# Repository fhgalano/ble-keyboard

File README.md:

# Overview 

This is an implementation of a bluetooth keyboard on an ESP32-C3 Devkit

# Code 

This was developed in conjunction with [keyboard](https://github.com/fhgalano/keyboard)

I'm using [esp32-nimble](https://github.com/taks/esp32-nimble) to handle the bluetooth conection. Most of the bluetooth connection code is taken from the examples. 

# Mechanical

I've been having fun with kicad scripting - I like the consistency it creates. It also helps with the tedious parts of routing a bunch of keyboard keys. Feel free to check it out [here](https://github.com/fhgalano/kicad-utilities), but I would describe the code as 'certified jank'

The PCB for the keyboard is reversible and uses cherry mx compatible hotswap sockets. It uses most of the gpio pins available on the devkit, but any remaining pins are made available through jst ph-k through hole connectors. It's also only two layers to make it cheaper to iterate through.

_**as of Feb 2025 I have only just placed the order for the first revision of the pcb, so I have no idea if it works. Use at your own risk. I'll update once I get it.**_

*Update: the board works but also has some large flaws - the biggest of which being that the devkit is positioned such that I need to remove several keys in order to program it. I'm lucky that I made this with hotswaps. I don't plan to update the board for a while, despite the flaws - I'll be implementing some new features (quick switching between bonded devices, power saving, using multiple devices as one wirelessly, layer indication leds, timers instead of blocking delays, and other stuff I notice while using it). Once those are done, then I'll look at redesigning the board*

I plan to make documentation eventually, since it's good practice. However, it isn't a huge priority since I am literally the only person aware that this project exists. Also, anyone looking to make a keyboard should probably be using something more feature rich like QMK, RMK, or Keyberon. Nevertheless, if documentation would help your project/learning then I'd be happy to add it in.

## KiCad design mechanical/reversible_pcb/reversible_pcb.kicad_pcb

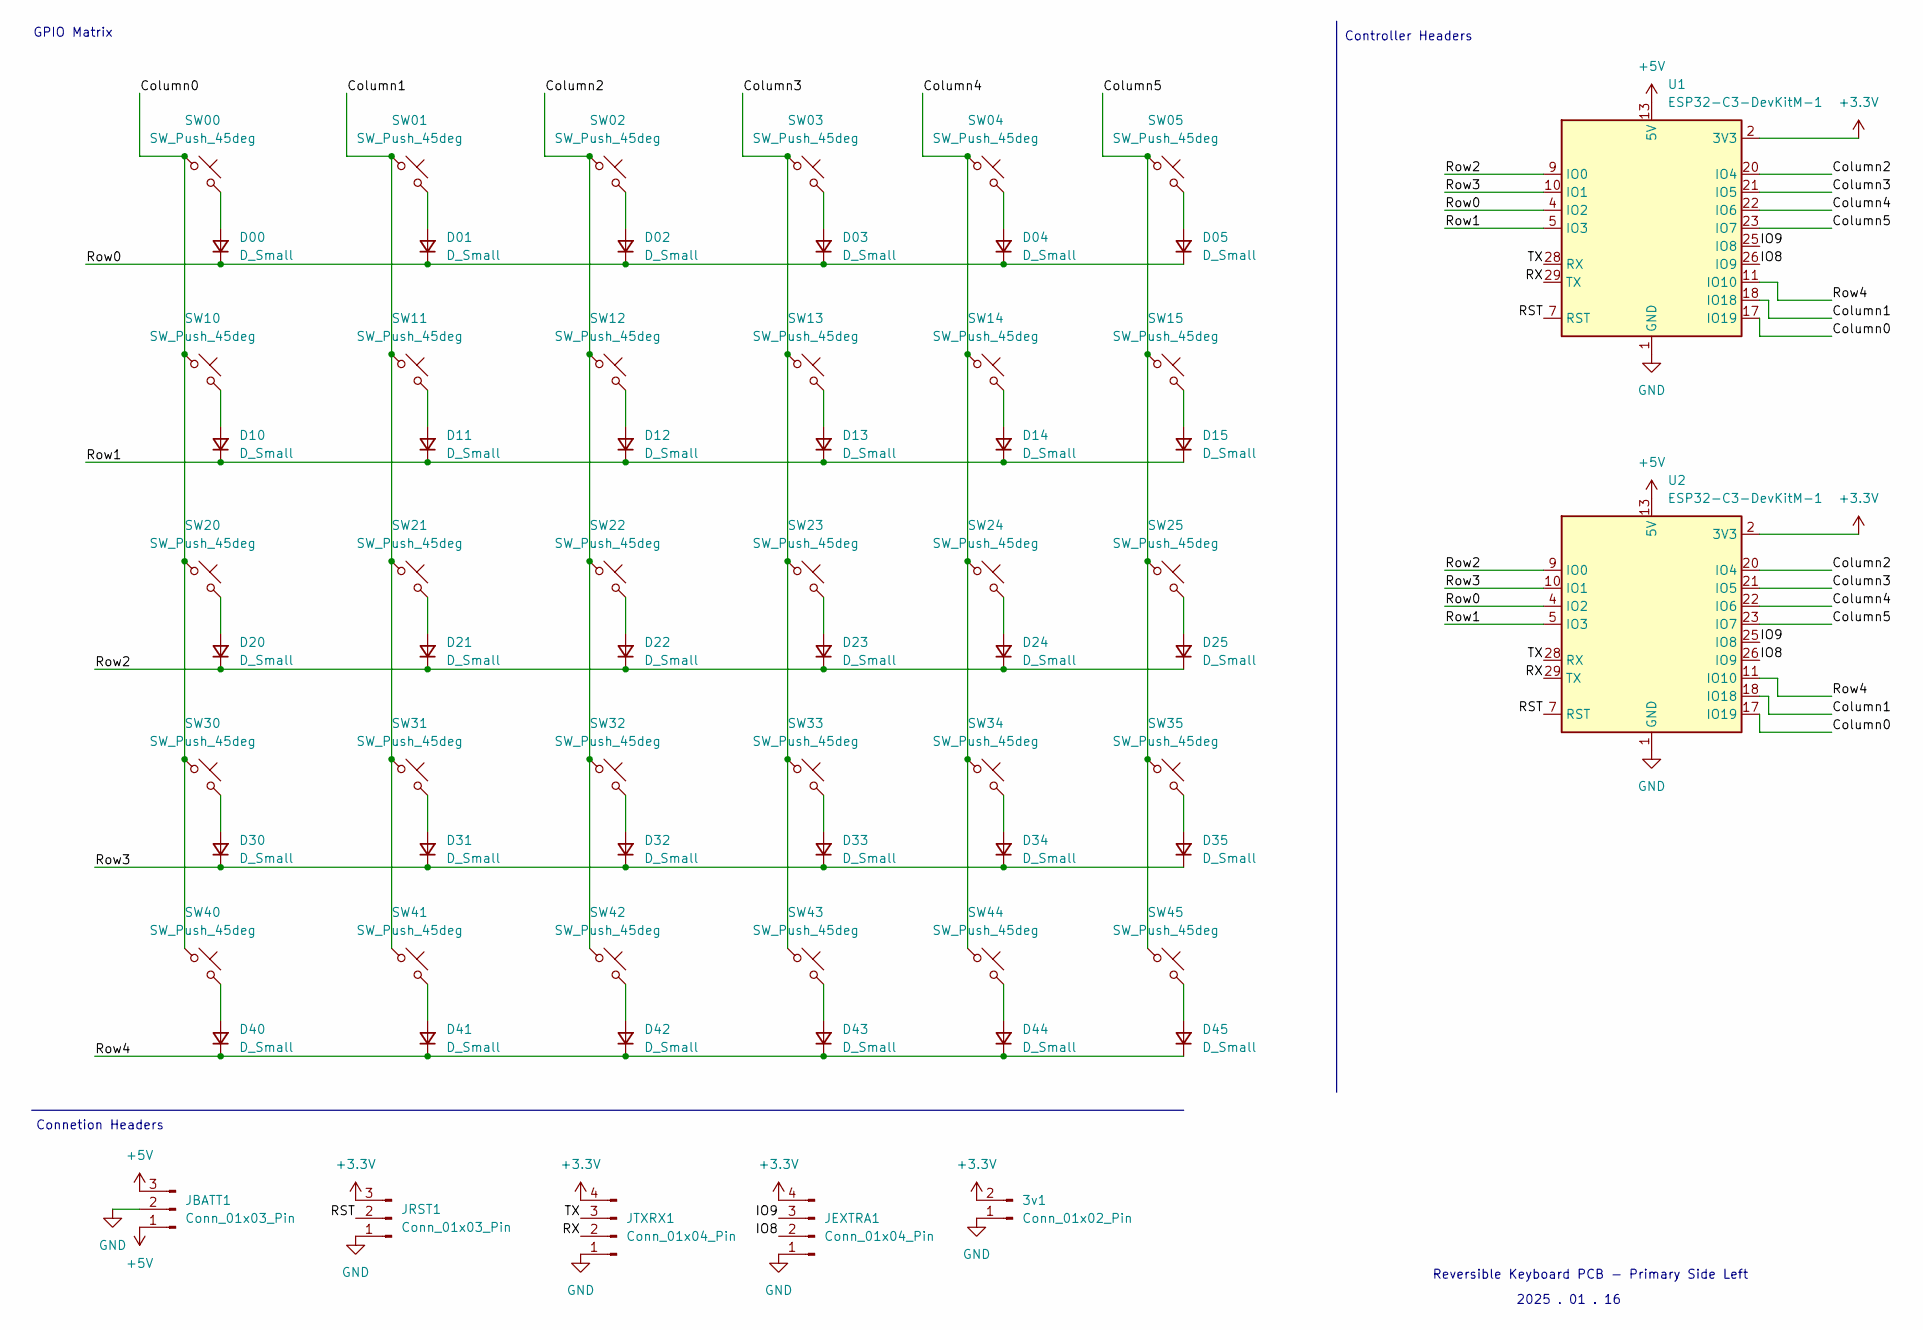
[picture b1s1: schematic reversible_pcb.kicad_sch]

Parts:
3v1: Conn_01x02_Pin; JST_PH_S2B-PH-K_1x02_P2.00mm_Horizontal
D00, D01, D02, D03, D04, D05, D10, D11, D12, D13, D14, D15, D20, D21, D22, D23, D24, D25, D30, D31, D32, D33, D34, D35, D40, D41, D42, D43, D44, D45: D_Small; D_T-1_P5.08mm_Horizontal_Double_Silkscreen
JBATT1: Conn_01x03_Pin; JST_PH_S3B-PH-K_1x03_P2.00mm_Horizontal
JEXTRA1: Conn_01x04_Pin; JST_PH_S4B-PH-K_1x04_P2.00mm_Horizontal
JRST1: Conn_01x03_Pin; JST_PH_S3B-PH-K_1x03_P2.00mm_Horizontal
JTXRX1: Conn_01x04_Pin; JST_PH_S4B-PH-K_1x04_P2.00mm_Horizontal
SW00, SW01, SW02, SW03, SW04, SW10, SW11, SW12, SW13, SW14, SW20, SW21, SW22, SW23, SW24, SW30, SW31, SW32, SW33, SW34, SW40, SW41, SW43, SW44, SW45: SW_Push_45deg; SW_Hotswap_Kailh_MX_reversible_1.00u
SW05, SW15, SW25, SW35: SW_Push_45deg; SW_Hotswap_Kailh_MX_reversible_1.25u
SW42: SW_Push_45deg; SW_Hotswap_Kailh_MX_reversible_1.50u_90deg
U1, U2: ESP32-C3-DevKitM-1

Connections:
+3.3V: 3v1.2, JEXTRA1.4, JRST1.3, JTXRX1.4, U1.2 (3V3), U1.3 (3V3), U2.2 (3V3), U2.3 (3V3)
+5V: JBATT1.1, JBATT1.3, U1.13 (5V), U1.14 (5V), U2.13 (5V), U2.14 (5V)
/Column0: SW00.1, SW10.1, SW20.1, SW30.1, SW40.1, U1.17 (IO19), U2.17 (IO19)
/Column1: SW01.1, SW11.1, SW21.1, SW31.1, SW41.1, U1.18 (IO18), U2.18 (IO18)
/Column2: SW02.1, SW12.1, SW22.1, SW32.1, SW42.1, U1.20 (IO4), U2.20 (IO4)
/Column3: SW03.1, SW13.1, SW23.1, SW33.1, SW43.1, U1.21 (IO5), U2.21 (IO5)
/Column4: SW04.1, SW14.1, SW24.1, SW34.1, SW44.1, U1.22 (IO6), U2.22 (IO6)
/Column5: SW05.1, SW15.1, SW25.1, SW35.1, SW45.1, U1.23 (IO7), U2.23 (IO7)
/IO8: JEXTRA1.2, U1.26 (IO9), U2.26 (IO9)
/IO9: JEXTRA1.3, U1.25 (IO8), U2.25 (IO8)
/RST: JRST1.2, U1.7 (RST), U2.7 (RST)
/RX: JTXRX1.2, U1.29 (TX), U2.29 (TX)
/Row0: D00.1 (K), D01.1 (K), D02.1 (K), D03.1 (K), D04.1 (K), D05.1 (K), U1.4 (IO2), U2.4 (IO2)
/Row1: D10.1 (K), D11.1 (K), D12.1 (K), D13.1 (K), D14.1 (K), D15.1 (K), U1.5 (IO3), U2.5 (IO3)
/Row2: D20.1 (K), D21.1 (K), D22.1 (K), D23.1 (K), D24.1 (K), D25.1 (K), U1.9 (IO0), U2.9 (IO0)
/Row3: D30.1 (K), D31.1 (K), D32.1 (K), D33.1 (K), D34.1 (K), D35.1 (K), U1.10 (IO1), U2.10 (IO1)
/Row4: D40.1 (K), D41.1 (K), D42.1 (K), D43.1 (K), D44.1 (K), D45.1 (K), U1.11 (IO10), U2.11 (IO10)
/TX: JTXRX1.3, U1.28 (RX), U2.28 (RX)
GND: 3v1.1, JBATT1.2, JEXTRA1.1, JRST1.1, JTXRX1.1, U1.1 (GND), U1.6 (GND), U1.8 (GND), U1.12 (GND), U1.15 (GND), U1.16 (GND), U1.19 (GND), U1.24 (GND), U1.27 (GND), U1.30 (GND), U2.1 (GND), U2.6 (GND), U2.8 (GND), U2.12 (GND), U2.15 (GND), U2.16 (GND), U2.19 (GND), U2.24 (GND), U2.27 (GND), U2.30 (GND)
unnamed: D00.2 (A), SW00.2
unnamed: D01.2 (A), SW01.2
unnamed: D02.2 (A), SW02.2
unnamed: D03.2 (A), SW03.2
unnamed: D04.2 (A), SW04.2
unnamed: D05.2 (A), SW05.2
unnamed: D10.2 (A), SW10.2
unnamed: D11.2 (A), SW11.2
unnamed: D12.2 (A), SW12.2
unnamed: D13.2 (A), SW13.2
unnamed: D14.2 (A), SW14.2
unnamed: D15.2 (A), SW15.2
unnamed: D20.2 (A), SW20.2
unnamed: D21.2 (A), SW21.2
unnamed: D22.2 (A), SW22.2
unnamed: D23.2 (A), SW23.2
unnamed: D24.2 (A), SW24.2
unnamed: D25.2 (A), SW25.2
unnamed: D30.2 (A), SW30.2
unnamed: D31.2 (A), SW31.2
unnamed: D32.2 (A), SW32.2
unnamed: D33.2 (A), SW33.2
unnamed: D34.2 (A), SW34.2
unnamed: D35.2 (A), SW35.2
unnamed: D40.2 (A), SW40.2
unnamed: D41.2 (A), SW41.2
unnamed: D42.2 (A), SW42.2
unnamed: D43.2 (A), SW43.2
unnamed: D44.2 (A), SW44.2
unnamed: D45.2 (A), SW45.2

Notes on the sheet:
Reversible Keyboard PCB - Primary Side Left
2025 . 01 . 16
Connetion Headers
Controller Headers
GPIO Matrix

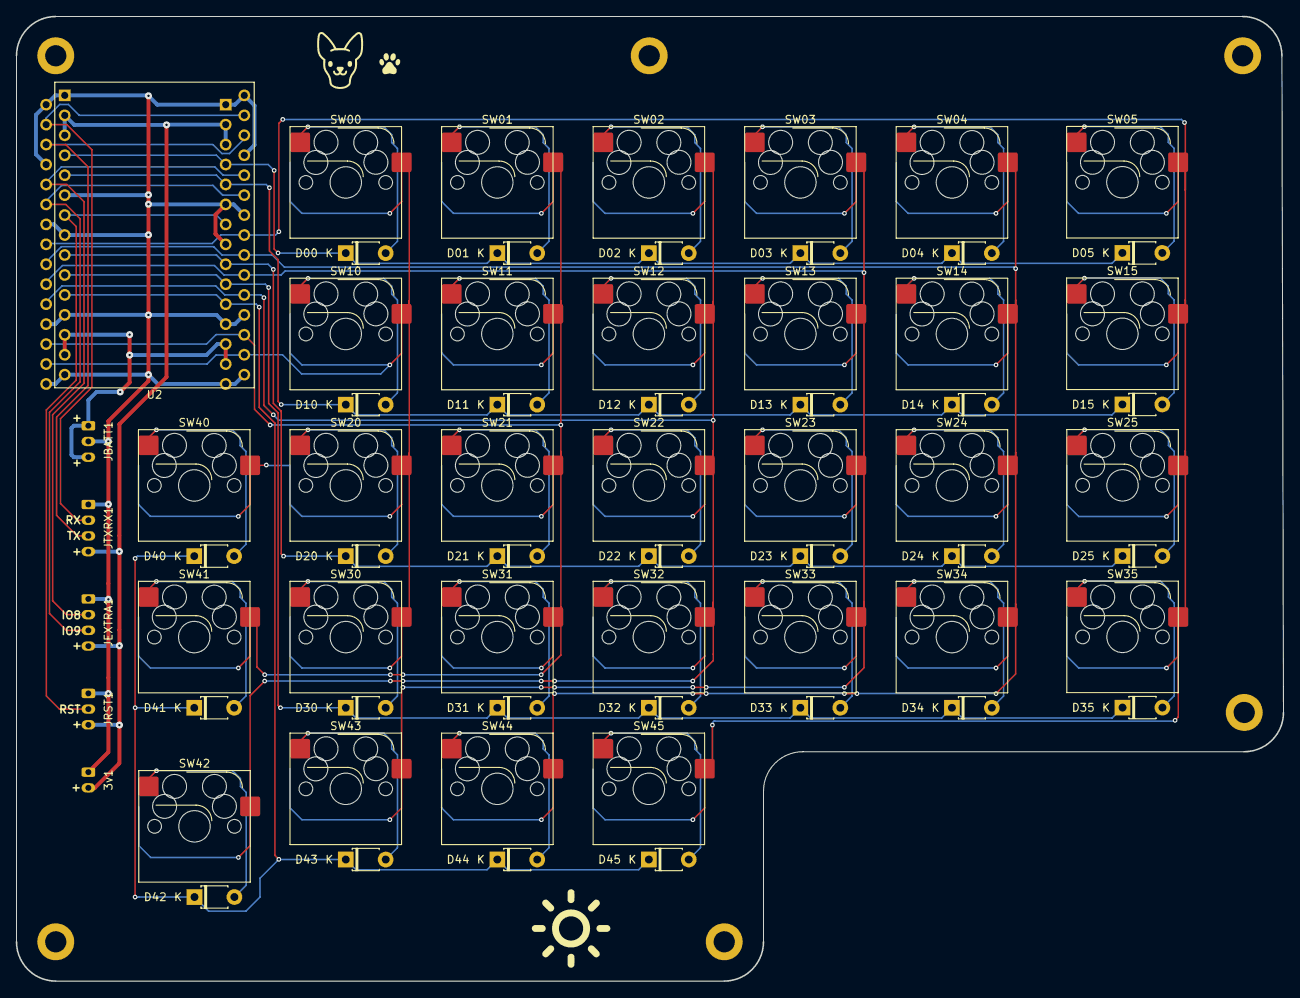
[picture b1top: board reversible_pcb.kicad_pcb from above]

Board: 2 copper layers, 161.3 x 122.8 mm, 67 parts (1 on the bottom side), 49 nets.

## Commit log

2025-01-12 initial commit; keyboard messages send correctly, but is not able to use gpio as input
2025-02-03 fixed polling logic issues
2025-02-03 added kicad files for main board
2025-02-03 fixes for ble connection issues
2025-02-03 added README
2025-02-14 removed backups covered by keyboard lib
2025-03-08 fixed issue related to esp dependencies
2025-03-08 added ios persistence so I could test on my phone
2025-03-08 updated to use correct gpio pins from the pcb, also using new lib features to create layers
2025-03-26 working (ugly) mvp for two keyboard halves acting as one device
2025-03-26 Authors
2025-03-26 removed local debug dep
